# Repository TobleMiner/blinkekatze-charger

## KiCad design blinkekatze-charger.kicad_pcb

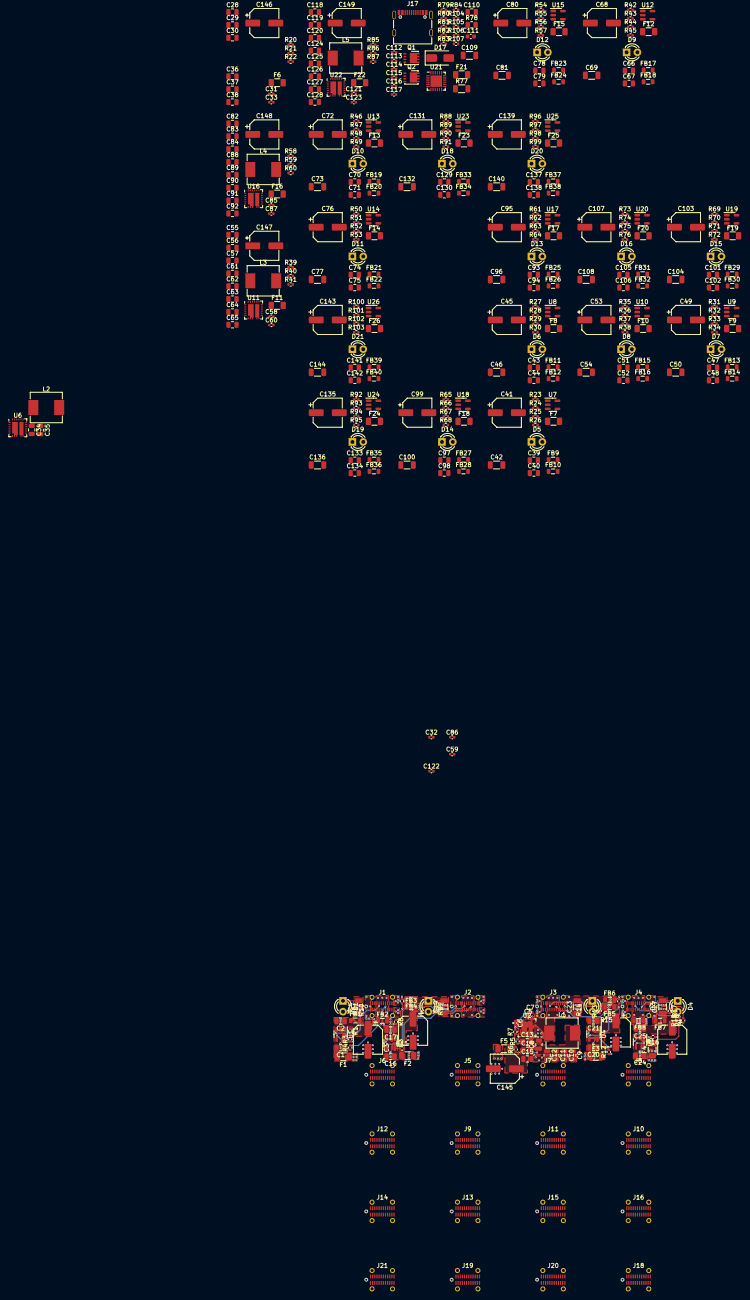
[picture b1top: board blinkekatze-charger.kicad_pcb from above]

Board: 4 copper layers, 397 parts (0 on the bottom side), 213 nets.

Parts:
C1, C2, C13, C14, C15, C16, C17, C20, C21, C24, C25, C28, C29, C30, C39, C40, C43, C44, C47, C48, C51, C52, C55, C56, C57, C66, C67, C70, C71, C74, C75, C78, C79, C82, C83, C84, C93, C94, C97, C98, C101, C102, C105, C106, C110, C118, C119, C120, C129, C130, C133, C134, C137, C138, C141, C142: 10uF; C_0805_2012Metric
C3, C18, C22, C26, C41, C45, C49, C53, C68, C72, C76, C80, C95, C99, C103, C107, C131, C135, C139, C143: 150uF; CP_Elec_6.3x7.7
C4, C19, C23, C27, C42, C46, C50, C54, C69, C73, C77, C81, C96, C100, C104, C108, C132, C136, C140, C144: 100nF 1206; C_1206_3216Metric
C5, C33, C60, C87, C112, C114, C116, C123: 1uF; C_0402_1005Metric
C6, C7, C31, C32, C58, C59, C85, C86, C113, C115, C117, C121, C122: 100nF; C_0402_1005Metric
C8, C9, C10, C11, C12, C34, C35, C36, C37, C38, C61, C62, C63, C64, C65, C88, C89, C90, C91, C92, C124, C125, C126, C127, C128: 22uF; C_0805_2012Metric
C109: 1nF; C_1206_3216Metric
C111: 1uF HV; C_0603_1608Metric
C145, C146, C147, C148, C149: 100uF; CP_Elec_6.3x7.7
D1, D2, D3, D4, D5, D6, D7, D8, D9, D10, D11, D12, D13, D14, D15, D16, D18, D19, D20, D21: RED; LED_D3.0mm
D17: SMAJ22A; D_SMA
F1, F2, F3, F4, F7, F8, F9, F10, F12, F13, F14, F15, F17, F18, F19, F20, F23, F24, F25, F26: 2A; Fuse_1206_3216Metric
F5, F6, F11, F16, F22: 3A; Fuse_1206_3216Metric
F21: 6A; Fuse_1206_3216Metric
FB1, FB2, FB3, FB4, FB5, FB6, FB7, FB8, FB9, FB10, FB11, FB12, FB13, FB14, FB15, FB16, FB17, FB18, FB19, FB20, FB21, FB22, FB23, FB24, FB25, FB26, FB27, FB28, FB29, FB30, FB31, FB32, FB33, FB34, FB35, FB36, FB37, FB38, FB39, FB40: 120R@100MHz 3A; L_0805_2012Metric
J1, J2, J3, J4, J5, J6, J7, J8, J9, J10, J11, J12, J13, J14, J15, J16, J18, J19, J20, J21: USB_C_Receptacle; USB_Type_C_Straight_C168703
J17: USB_C_Receptacle_USB2.0; USB_C_Receptacle_Palconn_UTC16-G
L1, L2, L3, L4, L5: 1.5uH; L_Sunlord_MWSA0603S
Q1, Q2: AON7534; DFN-8-FET_3x3mm_P0.65mm
R1, R8, R12, R16, R23, R27, R31, R35, R42, R46, R50, R54, R61, R65, R69, R73, R88, R92, R96, R100, R104, R106, R107: 4.7k; R_0402_1005Metric
R2, R9, R13, R17, R24, R28, R32, R36, R43, R47, R51, R55, R62, R66, R70, R74, R89, R93, R97, R101: 330R; R_0402_1005Metric
R3, R4, R10, R11, R14, R15, R18, R19, R25, R26, R29, R30, R33, R34, R37, R38, R44, R45, R48, R49, R52, R53, R56, R57, R63, R64, R67, R68, R71, R72, R75, R76, R90, R91, R94, R95, R98, R99, R102, R103, R105: 22k; R_0402_1005Metric
R5, R20, R39, R58, R85: 200k; R_0402_1005Metric
R6, R21, R40, R59, R86: 300k; R_0402_1005Metric
R7, R22, R41, R60, R87: 56k; R_0402_1005Metric
R77: 100k HV; R_1206_3216Metric
R78: 1R; R_0805_2012Metric
R79, R80, R81, R83: 10k; R_0402_1005Metric
R82, R84: 100k; R_0402_1005Metric
U1, U3, U4, U5, U7, U8, U9, U10, U12, U13, U14, U15, U17, U18, U19, U20, U23, U24, U25, U26: MT9700; SOT-23-5
U2, U6, U11, U16, U22: AOZ1267QI; QFN-23L
U21: CYPD3177; QFN-24-1EP_4x4mm_P0.5mm_EP2.7x2.7mm

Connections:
+3V3: C114.1, C115.1, R79.1, R80.1, R105.1, R106.2, U21.2 (VBUS_MAX), U21.23 (VDDD)
/Port group 1/Port 1/VIN: C8.1, C9.1, C10.1, C11.1, C12.1, F1.1, F2.1, F3.1, F4.1, L1.2, R6.1
/Port group 1/VCC: C5.1, U2.2 (EN), U2.21 (VCC)
/Port group 1/VIN: C117.1, F5.1, F6.1, F11.1, F16.1, F22.1, Q2.5 (D), R84.1, U21.11 (VDC_OUT)
/Port group 2/Port 1/VIN: C34.1, C35.1, C36.1, C37.1, C38.1, F7.1, F8.1, F9.1, F10.1, L2.2, R21.1
/Port group 2/VCC: C33.1, U6.2 (EN), U6.21 (VCC)
/Port group 3/Port 1/VIN: C61.1, C62.1, C63.1, C64.1, C65.1, F12.1, F13.1, F14.1, F15.1, L3.2, R40.1
/Port group 3/VCC: C60.1, U11.2 (EN), U11.21 (VCC)
/Port group 4/Port 1/VIN: C88.1, C89.1, C90.1, C91.1, C92.1, F17.1, F18.1, F19.1, F20.1, L4.2, R59.1
/Port group 4/VCC: C87.1, U16.2 (EN), U16.21 (VCC)
/Port group 5/Port 1/VIN: C124.1, C125.1, C126.1, C127.1, C128.1, F23.1, F24.1, F25.1, F26.1, L5.2, R86.1
/Port group 5/VCC: C123.1, U22.2 (EN), U22.21 (VCC)
GND: C1.2, C2.2, C3.2, C5.2, C6.2, C8.2, C9.2, C10.2, C11.2, C12.2, C13.2, C14.2, C15.2, C16.2, C17.2, C18.2, C20.2, C21.2, C22.2, C24.2, C25.2, C26.2, C28.2, C29.2, C30.2, C31.2, C33.2, C34.2, C35.2, C36.2, C37.2, C38.2, C39.2, C40.2, C41.2, C43.2, C44.2, C45.2, C47.2, C48.2, C49.2, C51.2, C52.2, C53.2, C55.2, C56.2, C57.2, C58.2, C60.2, C61.2, C62.2, C63.2, C64.2, C65.2, C66.2, C67.2, C68.2, C70.2, C71.2, C72.2, C74.2, C75.2, C76.2, C78.2, C79.2, C80.2, C82.2, C83.2, C84.2, C85.2, C87.2, C88.2, C89.2, C90.2, C91.2, C92.2, C93.2, C94.2, C95.2, C97.2, C98.2, C99.2, C101.2, C102.2, C103.2, C105.2, C106.2, C107.2, C109.2, C111.2, C112.2, C114.2, C115.2, C118.2, C119.2, C120.2, C121.2, C123.2, C124.2, C125.2, C126.2, C127.2, C128.2, C129.2, C130.2, C131.2, C133.2, C134.2, C135.2, C137.2, C138.2, C139.2, C141.2, C142.2, C143.2, C145.2, C146.2, C147.2, C148.2, C149.2, D17.2 (A2), FB2.2, FB4.2, FB6.2, FB8.2, FB10.2, FB12.2, FB14.2, FB16.2, FB18.2, FB20.2, FB22.2, FB24.2, FB26.2, FB28.2, FB30.2, FB32.2, FB34.2, FB36.2, FB38.2, FB40.2, J1.S1 (SHIELD), J2.S1 (SHIELD), J3.S1 (SHIELD), J4.S1 (SHIELD), J5.S1 (SHIELD), J6.S1 (SHIELD), J7.S1 (SHIELD), J8.S1 (SHIELD), J9.S1 (SHIELD), J10.S1 (SHIELD), J11.S1 (SHIELD), J12.S1 (SHIELD), J13.S1 (SHIELD), J14.S1 (SHIELD), J15.S1 (SHIELD), J16.S1 (SHIELD), J17.A1 (GND), J17.A12 (GND), J17.B1 (GND), J17.B12 (GND), J18.S1 (SHIELD), J19.S1 (SHIELD), J20.S1 (SHIELD), J21.S1 (SHIELD), R1.1, R7.2, R8.1, R12.1, R16.1, R22.2, R23.1, R27.1, R31.1, R35.1, R41.2, R42.1, R46.1, R50.1, R54.1, R60.2, R61.1, R65.1, R69.1, R73.1, R77.2, R78.2, R87.2, R88.1, R92.1, R96.1, R100.1, R104.1, R107.1, U1.2 (GND), U2.3 (~PFM), U2.4 (AGND), U2.12 (PGND), U2.13 (PGND), U2.14 (PGND), U2.15 (PGND), U2.19 (PGND), U3.2 (GND), U4.2 (GND), U5.2 (GND), U6.3 (~PFM), U6.4 (AGND), U6.12 (PGND), U6.13 (PGND), U6.14 (PGND), U6.15 (PGND), U6.19 (PGND), U7.2 (GND), U8.2 (GND), U9.2 (GND), U10.2 (GND), U11.3 (~PFM), U11.4 (AGND), U11.12 (PGND), U11.13 (PGND), U11.14 (PGND), U11.15 (PGND), U11.19 (PGND), U12.2 (GND), U13.2 (GND), U14.2 (GND), U15.2 (GND), U16.3 (~PFM), U16.4 (AGND), U16.12 (PGND), U16.13 (PGND), U16.14 (PGND), U16.15 (PGND), U16.19 (PGND), U17.2 (GND), U18.2 (GND), U19.2 (GND), U20.2 (GND), U21.6 (ISNK_FINE), U21.19 (GND), U21.22 (VSS), U21.25 (GND), U22.3 (~PFM), U22.4 (AGND), U22.12 (PGND), U22.13 (PGND), U22.14 (PGND), U22.15 (PGND), U22.19 (PGND), U23.2 (GND), U24.2 (GND), U25.2 (GND), U26.2 (GND)
IN: C13.1, C14.1, C15.1, C28.1, C29.1, C30.1, C55.1, C56.1, C57.1, C82.1, C83.1, C84.1, C118.1, C119.1, C120.1, C145.1, C146.1, C147.1, C148.1, C149.1, F5.2, F6.2, F11.2, F16.2, F22.2, R5.1, R20.1, R39.1, R58.1, R85.1, U2.7 (AIN), U2.8 (IN), U2.9 (IN), U2.22 (IN), U6.7 (AIN), U6.8 (IN), U6.9 (IN), U6.22 (IN), U11.7 (AIN), U11.8 (IN), U11.9 (IN), U11.22 (IN), U16.7 (AIN), U16.8 (IN), U16.9 (IN), U16.22 (IN), U22.7 (AIN), U22.8 (IN), U22.9 (IN), U22.22 (IN)
unnamed: C4.1, FB1.2, J1.A4 (VBUS), J1.A9 (VBUS), J1.B4 (VBUS), J1.B9 (VBUS), R2.2
unnamed: C7.2, L1.1, U2.10 (LX), U2.11 (LX), U2.16 (LX), U2.17 (LX), U2.18 (LX)
unnamed: C19.1, FB3.2, J2.A4 (VBUS), J2.A9 (VBUS), J2.B4 (VBUS), J2.B9 (VBUS), R9.2
unnamed: C23.1, FB5.2, J3.A4 (VBUS), J3.A9 (VBUS), J3.B4 (VBUS), J3.B9 (VBUS), R13.2
unnamed: C27.1, FB7.2, J4.A4 (VBUS), J4.A9 (VBUS), J4.B4 (VBUS), J4.B9 (VBUS), R17.2
unnamed: C32.2, L2.1, U6.10 (LX), U6.11 (LX), U6.16 (LX), U6.17 (LX), U6.18 (LX)
unnamed: C42.1, FB9.2, J5.A4 (VBUS), J5.A9 (VBUS), J5.B4 (VBUS), J5.B9 (VBUS), R24.2
unnamed: C46.1, FB11.2, J6.A4 (VBUS), J6.A9 (VBUS), J6.B4 (VBUS), J6.B9 (VBUS), R28.2
unnamed: C50.1, FB13.2, J7.A4 (VBUS), J7.A9 (VBUS), J7.B4 (VBUS), J7.B9 (VBUS), R32.2
unnamed: C54.1, FB15.2, J8.A4 (VBUS), J8.A9 (VBUS), J8.B4 (VBUS), J8.B9 (VBUS), R36.2
unnamed: C59.2, L3.1, U11.10 (LX), U11.11 (LX), U11.16 (LX), U11.17 (LX), U11.18 (LX)
unnamed: C69.1, FB17.2, J9.A4 (VBUS), J9.A9 (VBUS), J9.B4 (VBUS), J9.B9 (VBUS), R43.2
unnamed: C73.1, FB19.2, J10.A4 (VBUS), J10.A9 (VBUS), J10.B4 (VBUS), J10.B9 (VBUS), R47.2
unnamed: C77.1, FB21.2, J11.A4 (VBUS), J11.A9 (VBUS), J11.B4 (VBUS), J11.B9 (VBUS), R51.2
unnamed: C81.1, FB23.2, J12.A4 (VBUS), J12.A9 (VBUS), J12.B4 (VBUS), J12.B9 (VBUS), R55.2
unnamed: C86.2, L4.1, U16.10 (LX), U16.11 (LX), U16.16 (LX), U16.17 (LX), U16.18 (LX)
unnamed: C96.1, FB25.2, J13.A4 (VBUS), J13.A9 (VBUS), J13.B4 (VBUS), J13.B9 (VBUS), R62.2
unnamed: C100.1, FB27.2, J14.A4 (VBUS), J14.A9 (VBUS), J14.B4 (VBUS), J14.B9 (VBUS), R66.2
unnamed: C104.1, FB29.2, J15.A4 (VBUS), J15.A9 (VBUS), J15.B4 (VBUS), J15.B9 (VBUS), R70.2
unnamed: C108.1, FB31.2, J16.A4 (VBUS), J16.A9 (VBUS), J16.B4 (VBUS), J16.B9 (VBUS), R74.2
unnamed: C110.2, R78.1
unnamed: C116.1, Q1.1 (S), Q1.2 (S), Q1.3 (S), Q2.1 (S), Q2.2 (S), Q2.3 (S), R83.1
unnamed: C122.2, L5.1, U22.10 (LX), U22.11 (LX), U22.16 (LX), U22.17 (LX), U22.18 (LX)
unnamed: C132.1, FB33.2, J18.A4 (VBUS), J18.A9 (VBUS), J18.B4 (VBUS), J18.B9 (VBUS), R89.2
unnamed: C136.1, FB35.2, J19.A4 (VBUS), J19.A9 (VBUS), J19.B4 (VBUS), J19.B9 (VBUS), R93.2
unnamed: C140.1, FB37.2, J20.A4 (VBUS), J20.A9 (VBUS), J20.B4 (VBUS), J20.B9 (VBUS), R97.2
unnamed: C144.1, FB39.2, J21.A4 (VBUS), J21.A9 (VBUS), J21.B4 (VBUS), J21.B9 (VBUS), R101.2
unnamed: D1.2 (A), R2.1
unnamed: C4.2, D1.1 (K), FB2.1, J1.A1 (GND), J1.A12 (GND), J1.B1 (GND), J1.B12 (GND)
unnamed: D2.2 (A), R9.1
unnamed: C19.2, D2.1 (K), FB4.1, J2.A1 (GND), J2.A12 (GND), J2.B1 (GND), J2.B12 (GND)
unnamed: D3.2 (A), R13.1
unnamed: C23.2, D3.1 (K), FB6.1, J3.A1 (GND), J3.A12 (GND), J3.B1 (GND), J3.B12 (GND)
unnamed: D4.2 (A), R17.1
unnamed: C27.2, D4.1 (K), FB8.1, J4.A1 (GND), J4.A12 (GND), J4.B1 (GND), J4.B12 (GND)
unnamed: D5.2 (A), R24.1
unnamed: C42.2, D5.1 (K), FB10.1, J5.A1 (GND), J5.A12 (GND), J5.B1 (GND), J5.B12 (GND)
unnamed: D6.2 (A), R28.1
unnamed: C46.2, D6.1 (K), FB12.1, J6.A1 (GND), J6.A12 (GND), J6.B1 (GND), J6.B12 (GND)
unnamed: D7.2 (A), R32.1
unnamed: C50.2, D7.1 (K), FB14.1, J7.A1 (GND), J7.A12 (GND), J7.B1 (GND), J7.B12 (GND)
unnamed: D8.2 (A), R36.1
unnamed: C54.2, D8.1 (K), FB16.1, J8.A1 (GND), J8.A12 (GND), J8.B1 (GND), J8.B12 (GND)
unnamed: D9.2 (A), R43.1
unnamed: C69.2, D9.1 (K), FB18.1, J9.A1 (GND), J9.A12 (GND), J9.B1 (GND), J9.B12 (GND)
unnamed: D10.2 (A), R47.1
unnamed: C73.2, D10.1 (K), FB20.1, J10.A1 (GND), J10.A12 (GND), J10.B1 (GND), J10.B12 (GND)
unnamed: D11.2 (A), R51.1
unnamed: C77.2, D11.1 (K), FB22.1, J11.A1 (GND), J11.A12 (GND), J11.B1 (GND), J11.B12 (GND)
unnamed: D12.2 (A), R55.1
unnamed: C81.2, D12.1 (K), FB24.1, J12.A1 (GND), J12.A12 (GND), J12.B1 (GND), J12.B12 (GND)
unnamed: D13.2 (A), R62.1
unnamed: C96.2, D13.1 (K), FB26.1, J13.A1 (GND), J13.A12 (GND), J13.B1 (GND), J13.B12 (GND)
unnamed: D14.2 (A), R66.1
unnamed: C100.2, D14.1 (K), FB28.1, J14.A1 (GND), J14.A12 (GND), J14.B1 (GND), J14.B12 (GND)
unnamed: D15.2 (A), R70.1
unnamed: C104.2, D15.1 (K), FB30.1, J15.A1 (GND), J15.A12 (GND), J15.B1 (GND), J15.B12 (GND)
unnamed: D16.2 (A), R74.1
unnamed: C108.2, D16.1 (K), FB32.1, J16.A1 (GND), J16.A12 (GND), J16.B1 (GND), J16.B12 (GND)
unnamed: C110.1, C111.1, C113.1, D17.1 (A1), F21.2, Q1.5 (D), R82.1, U21.18 (VBUS_IN)
unnamed: D18.2 (A), R89.1
unnamed: C132.2, D18.1 (K), FB34.1, J18.A1 (GND), J18.A12 (GND), J18.B1 (GND), J18.B12 (GND)
unnamed: D19.2 (A), R93.1
unnamed: C136.2, D19.1 (K), FB36.1, J19.A1 (GND), J19.A12 (GND), J19.B1 (GND), J19.B12 (GND)
unnamed: D20.2 (A), R97.1
unnamed: C140.2, D20.1 (K), FB38.1, J20.A1 (GND), J20.A12 (GND), J20.B1 (GND), J20.B12 (GND)
unnamed: D21.2 (A), R101.1
unnamed: C144.2, D21.1 (K), FB40.1, J21.A1 (GND), J21.A12 (GND), J21.B1 (GND), J21.B12 (GND)
unnamed: F21.1, J17.A4 (VBUS), J17.A9 (VBUS), J17.B4 (VBUS), J17.B9 (VBUS)
unnamed: J1.A5 (CC1), R3.2
unnamed: J1.B5 (CC2), R4.2
unnamed: J2.A5 (CC1), R10.2
unnamed: J2.B5 (CC2), R11.2
unnamed: J3.A5 (CC1), R14.2
unnamed: J3.B5 (CC2), R15.2
unnamed: J4.A5 (CC1), R18.2
unnamed: J4.B5 (CC2), R19.2
unnamed: J5.A5 (CC1), R25.2
unnamed: J5.B5 (CC2), R26.2
unnamed: J6.A5 (CC1), R29.2
unnamed: J6.B5 (CC2), R30.2
unnamed: J7.A5 (CC1), R33.2
unnamed: J7.B5 (CC2), R34.2
unnamed: J8.A5 (CC1), R37.2
unnamed: J8.B5 (CC2), R38.2
unnamed: J9.A5 (CC1), R44.2
unnamed: J9.B5 (CC2), R45.2
unnamed: J10.A5 (CC1), R48.2
unnamed: J10.B5 (CC2), R49.2
unnamed: J11.A5 (CC1), R52.2
unnamed: J11.B5 (CC2), R53.2
unnamed: J12.A5 (CC1), R56.2
unnamed: J12.B5 (CC2), R57.2
unnamed: J13.A5 (CC1), R63.2
unnamed: J13.B5 (CC2), R64.2
unnamed: J14.A5 (CC1), R67.2
unnamed: J14.B5 (CC2), R68.2
unnamed: J15.A5 (CC1), R71.2
unnamed: J15.B5 (CC2), R72.2
unnamed: J16.A5 (CC1), R75.2
unnamed: J16.B5 (CC2), R76.2
unnamed: J17.A5 (CC1), U21.15 (CC1)
unnamed: J17.B5 (CC2), U21.14 (CC2)
unnamed: C109.1, J17.S1 (SHIELD), R77.1
unnamed: J18.A5 (CC1), R90.2
unnamed: J18.B5 (CC2), R91.2
unnamed: J19.A5 (CC1), R94.2
unnamed: J19.B5 (CC2), R95.2
unnamed: J20.A5 (CC1), R98.2
unnamed: J20.B5 (CC2), R99.2
unnamed: J21.A5 (CC1), R102.2
unnamed: J21.B5 (CC2), R103.2
unnamed: C113.2, C116.2, C117.2, Q1.4 (G), Q2.4 (G), R81.1, R82.2, R83.2, R84.2
unnamed: C1.1, F1.2, R3.1, R4.1, U1.4 (ON), U1.5 (IN)
unnamed: C2.1, C3.1, FB1.1, U1.1 (OUT)
unnamed: R1.2, U1.3 (SET)
unnamed: C7.1, U2.20 (BST)
unnamed: R6.2, R7.1, U2.5 (FB)
unnamed: C6.1, U2.23 (SS)
unnamed: R5.2, U2.6 (TON)
unnamed: C16.1, F2.2, R10.1, R11.1, U3.4 (ON), U3.5 (IN)
unnamed: C17.1, C18.1, FB3.1, U3.1 (OUT)
unnamed: R8.2, U3.3 (SET)
unnamed: C20.1, F3.2, R14.1, R15.1, U4.4 (ON), U4.5 (IN)
unnamed: C21.1, C22.1, FB5.1, U4.1 (OUT)
unnamed: R12.2, U4.3 (SET)
unnamed: C24.1, F4.2, R18.1, R19.1, U5.4 (ON), U5.5 (IN)
unnamed: C25.1, C26.1, FB7.1, U5.1 (OUT)
unnamed: R16.2, U5.3 (SET)
unnamed: C32.1, U6.20 (BST)
unnamed: R21.2, R22.1, U6.5 (FB)
unnamed: C31.1, U6.23 (SS)
unnamed: R20.2, U6.6 (TON)
unnamed: C39.1, F7.2, R25.1, R26.1, U7.4 (ON), U7.5 (IN)
unnamed: C40.1, C41.1, FB9.1, U7.1 (OUT)
unnamed: R23.2, U7.3 (SET)
unnamed: C43.1, F8.2, R29.1, R30.1, U8.4 (ON), U8.5 (IN)
unnamed: C44.1, C45.1, FB11.1, U8.1 (OUT)
unnamed: R27.2, U8.3 (SET)
unnamed: C47.1, F9.2, R33.1, R34.1, U9.4 (ON), U9.5 (IN)
unnamed: C48.1, C49.1, FB13.1, U9.1 (OUT)
unnamed: R31.2, U9.3 (SET)
unnamed: C51.1, F10.2, R37.1, R38.1, U10.4 (ON), U10.5 (IN)
unnamed: C52.1, C53.1, FB15.1, U10.1 (OUT)
unnamed: R35.2, U10.3 (SET)
unnamed: C59.1, U11.20 (BST)
unnamed: R40.2, R41.1, U11.5 (FB)
unnamed: C58.1, U11.23 (SS)
unnamed: R39.2, U11.6 (TON)
unnamed: C66.1, F12.2, R44.1, R45.1, U12.4 (ON), U12.5 (IN)
unnamed: C67.1, C68.1, FB17.1, U12.1 (OUT)
unnamed: R42.2, U12.3 (SET)
unnamed: C70.1, F13.2, R48.1, R49.1, U13.4 (ON), U13.5 (IN)
unnamed: C71.1, C72.1, FB19.1, U13.1 (OUT)
unnamed: R46.2, U13.3 (SET)
unnamed: C74.1, F14.2, R52.1, R53.1, U14.4 (ON), U14.5 (IN)
unnamed: C75.1, C76.1, FB21.1, U14.1 (OUT)
unnamed: R50.2, U14.3 (SET)
unnamed: C78.1, F15.2, R56.1, R57.1, U15.4 (ON), U15.5 (IN)
unnamed: C79.1, C80.1, FB23.1, U15.1 (OUT)
unnamed: R54.2, U15.3 (SET)
unnamed: C86.1, U16.20 (BST)
unnamed: R59.2, R60.1, U16.5 (FB)
unnamed: C85.1, U16.23 (SS)
unnamed: R58.2, U16.6 (TON)
unnamed: C93.1, F17.2, R63.1, R64.1, U17.4 (ON), U17.5 (IN)
unnamed: C94.1, C95.1, FB25.1, U17.1 (OUT)
unnamed: R61.2, U17.3 (SET)
unnamed: C97.1, F18.2, R67.1, R68.1, U18.4 (ON), U18.5 (IN)
unnamed: C98.1, C99.1, FB27.1, U18.1 (OUT)
unnamed: R65.2, U18.3 (SET)
unnamed: C101.1, F19.2, R71.1, R72.1, U19.4 (ON), U19.5 (IN)
unnamed: C102.1, C103.1, FB29.1, U19.1 (OUT)
unnamed: R69.2, U19.3 (SET)
unnamed: C105.1, F20.2, R75.1, R76.1, U20.4 (ON), U20.5 (IN)
unnamed: C106.1, C107.1, FB31.1, U20.1 (OUT)
unnamed: R73.2, U20.3 (SET)
unnamed: R79.2, U21.13 (HPI_SCL)
unnamed: R80.2, U21.12 (HPI_SDA)
unnamed: R106.1, R107.2, U21.5 (ISNK_COARSE)
unnamed: R81.2, U21.3 (VBUS_FET_EN)
unnamed: R104.2, R105.2, U21.1 (VBUS_MIN)
unnamed: C112.1, U21.24 (VCCD)
unnamed: C122.1, U22.20 (BST)
unnamed: R86.2, R87.1, U22.5 (FB)
unnamed: C121.1, U22.23 (SS)
unnamed: R85.2, U22.6 (TON)
unnamed: C129.1, F23.2, R90.1, R91.1, U23.4 (ON), U23.5 (IN)
unnamed: C130.1, C131.1, FB33.1, U23.1 (OUT)
unnamed: R88.2, U23.3 (SET)
unnamed: C133.1, F24.2, R94.1, R95.1, U24.4 (ON), U24.5 (IN)
unnamed: C134.1, C135.1, FB35.1, U24.1 (OUT)
unnamed: R92.2, U24.3 (SET)
unnamed: C137.1, F25.2, R98.1, R99.1, U25.4 (ON), U25.5 (IN)
unnamed: C138.1, C139.1, FB37.1, U25.1 (OUT)
unnamed: R96.2, U25.3 (SET)
unnamed: C141.1, F26.2, R102.1, R103.1, U26.4 (ON), U26.5 (IN)
unnamed: C142.1, C143.1, FB39.1, U26.1 (OUT)
unnamed: R100.2, U26.3 (SET)

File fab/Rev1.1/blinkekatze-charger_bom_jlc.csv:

"Comment","Designator","Footprint","LCSC Part Number"
"150uF","C3,C18,C22,C26,C41,C45,C49,C53,C68,C72,C76,C80,C95,C99,C103,C107,C131,C135,C139,C143","CP_Elec_6.3x7.7","C250091"
"100nF 1206","C4,C19,C23,C27,C42,C46,C50,C54,C69,C73,C77,C81,C96,C100,C104,C108,C132,C136,C140,C144","C_1206_3216Metric","C24497"
"22uF","C8,C9,C10,C11,C12,C34,C35,C36,C37,C38,C61,C62,C63,C64,C65,C88,C89,C90,C91,C92,C124,C125,C126,C127,C128","C_0805_2012Metric","C45783"
"2.2uF","C109","C_0805_2012Metric","C49217"
"10uF","C110,C1,C2,C13,C14,C15,C16,C17,C20,C21,C24,C25,C28,C29,C30,C39,C40,C43,C44,C47,C48,C51,C52,C55,C56,C57,C66,C67,C70,C71,C74,C75,C78,C79,C82,C83,C84,C93,C94,C97,C98,C101,C102,C105,C106,C118,C119,C120,C129,C130,C133,C134,C137,C138,C141,C142","C_0805_2012Metric","C440198"
"1uF HV","C111","C_0603_1608Metric","C15849"
"1uF","C112,C114,C116,C5,C33,C60,C87,C123","C_0402_1005Metric","C52923"
"100nF","C113,C115,C117,C6,C7,C31,C32,C58,C59,C85,C86,C121,C122","C_0402_1005Metric","C1525"
"100uF","C145,C146,C147,C148,C149","CP_Elec_6.3x7.7","C5361261"
"10uF 0603","C150","C_0402_1005Metric","C96446"
"SMAJ22A","D17","D_SMA","C309875"
"P6SMB6.8CA","D22,D23,D24,D25,D26","D_SMB","C78395"
"2A","F1,F2,F3,F4,F7,F8,F9,F10,F12,F13,F14,F15,F17,F18,F19,F20,F23,F24,F25,F26","Fuse_1206_3216Metric","C187611"
"3A","F5,F6,F11,F16,F22","Fuse_1206_3216Metric","C553935"
"6A","F21","Fuse_1206_3216Metric","C183161"
"120R@100MHz 3A","FB1,FB2,FB3,FB4,FB5,FB6,FB7,FB8,FB9,FB10,FB11,FB12,FB13,FB14,FB15,FB16,FB17,FB18,FB19,FB20,FB21,FB22,FB23,FB24,FB25,FB26,FB27,FB28,FB29,FB30,FB31,FB32,FB33,FB34,FB35,FB36,FB37,FB38,FB39,FB40","L_0805_2012Metric","C79382"
"USB_C_Receptacle","J1,J2,J3,J4,J5,J6,J7,J8,J9,J10,J11,J12,J13,J14,J15,J16,J18,J19,J20,J21","USB_Type_C_Straight_C168703","C168703"
"USB_C_Receptacle_USB2.0","J17","USB_C_Receptacle_Palconn_UTC16-G","C167321"
"4.7uH","L1,L2,L3,L4,L5","L_Sunlord_MWSA0605S","C5127340"
"AP90P03Q","Q1,Q2","DFN-8-FET_3x3mm_P0.65mm","C2849567"
"3.9k","R1,R8,R12,R16,R23,R27,R31,R35,R42,R46,R50,R54,R61,R65,R69,R73,R88,R92,R96,R100","R_0402_1005Metric","C51721"
"680R","R2,R9,R13,R17,R24,R28,R32,R36,R43,R47,R51,R55,R62,R66,R70,R74,R89,R93,R97,R101","R_0402_1005Metric","C25130"
"300k","R5,R6,R20,R21,R39,R40,R58,R59,R85,R86","R_0402_1005Metric","C25774"
"56k","R7,R22,R41,R60,R87","R_0402_1005Metric","C25796"
"1R","R78","R_0805_2012Metric","C25271"
"10k","R79,R80,R77,R108,R109,R110,R111","R_0402_1005Metric","C25744"
"100k","R81,R83","R_0402_1005Metric","C25741"
"1M","R82,R84","R_0402_1005Metric","C26083"
"4.7k","R104,R106,R107","R_0402_1005Metric","C25900"
"22k","R105,R3,R4,R10,R11,R14,R15,R18,R19,R25,R26,R29,R30,R33,R34,R37,R38,R44,R45,R48,R49,R52,R53,R56,R57,R63,R64,R67,R68,R71,R72,R75,R76,R90,R91,R94,R95,R98,R99,R102,R103","R_0402_1005Metric","C25768"
"0R","R112,R113,R114,R115,R116","R_0402_1005Metric","C17168"
"MT9700","U1,U3,U4,U5,U7,U8,U9,U10,U12,U13,U14,U15,U17,U18,U19,U20,U23,U24,U25,U26","SOT-23-5","C89855"
"AOZ1267QI","U2,U6,U11,U16,U22","QFN-23L","C2072052"
"CYPD3177","U21","QFN-24-1EP_4x4mm_P0.5mm_EP2.7x2.7mm","C2959321"
"HT7550-1-SOT89","U27","SOT-89-3","C16106"

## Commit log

2023-11-14 Layout group 1 port 4
2023-11-14 Finish group 1 layout
2023-11-14 Optimize bulk capacitor placement
2023-11-14 Finish layout
2023-11-14 Hide all silkscreen designators
2023-11-14 Fix GND zone connectivity on leftmost port column
2023-11-14 Supply regulator enable from CYPD LDO
2023-11-19 Add initial case design
2023-11-19 Consolidate bom items
2023-11-19 Fix LED partnumber
2023-11-19 case: add cutout for TVS
2023-11-24 Add TVS to port groups
2023-11-25 Advertise all charging ports as DCP
2023-11-26 case SLM DFM
2023-12-03 Optimize switch mode efficiency
    - Reduce switching frequency by one third
    - Increase inductor size
    - Use power stages with lower Rds(ON)
2023-12-04 Add 5V auxiliary supply
2023-12-04 Add plane for improved auxiliary regulator power dissipation
2023-12-04 Reduce LED drive current
    The LEDs are very bright when driven with a full 10mA.
    Reduce the drive current a bit to make them less intense.
2024-01-22 Do not populate buck converter VCC jumpers
2024-01-22 Add Rev1.1 fabrication files
2024-02-03 case: adjust for JLC SLM tolerances
2024-02-03 Reduce weight of bottom case shell
    - Reduce bottom wall thickness to 1.5mm
    - Remove inner walls
2024-02-03 Reduce outer wall thickness of bottom case to 1.5mm
